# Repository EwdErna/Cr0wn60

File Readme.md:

# Cr0wn60

Cr0wn60 配下の特徴を持つキーボードです。

- TreadStone 配列ベースの左右対称配列
- RP2040 採用の PCB
- Friction O-ring Mount の 3 ピースケース

ファームウェアは以下のリポジトリから取得可能です。  
[Ewderna/qmk_firmware ewderna_22 branch](https://github.com/EwdErna/qmk_firmware/tree/dev/ewderna_22)

## Build Guide

### 同梱物

- PCB
  - デフォルトのファームウェアを書き込み済み
- スイッチプレート
- ケース
  - トップケース
  - ミドルプレート
  - ボトムケース
- O-ring ID185x3.55mm
- Unified Daughter Board S1 / molex Pico EasyMate Cable

> [!Note]  
> ProtoType 版ではスイッチプレート、ケースはデータのみの配布となります。  
> また、O-ring については付属しません。ご自身で購入をお願いします。

### 別途必要なもの

- キースイッチ x60
  - Cherry MX 互換のみ対応
- スタビライザー
  - PCBマウント 2U x3
- LED x15 (Optional)
  - SK6812MINI-E 互換品
- USB Type-C ケーブル
- キーキャップ x60
  - 1U x48
  - 1.25U x5
  - 1.5U x2
  - 1.75U x2
  - 2.25U x3

### 組み立て手順

#### LEDのはんだ付け(Optional)

15個のLEDをはんだ付けします。  

#### スタビライザーの取り付け

PCBにスタビライザーを取り付けます。  
PCB表面にスタビライザーのワイヤー側を示すシルクがあります。  
向きを間違えないよう注意してください。

#### スイッチプレートにキースイッチの取り付け

すべてのキースイッチをスイッチプレートに取り付けます。

#### キースイッチのはんだ付け

プレートごとキースイッチをPCBに取り付け、裏面からはんだ付けします。

#### 動作確認

UDBに付属のケーブルをUDB、PCBそれぞれのハウジングに取り付けます。  
PCとUDBをType-Cケーブルでつなぎ、[Remap](https://remap-keys.app)に接続します。  
CUSTOMIZE YOUR KEYBOARDからCr0wn60を選択したのち、Test Matrixモードを使用し全キーが反応することを確認します。  
オプションのLEDを取り付けている場合もここで確認します。  
> [!TIP]  
> LEDが途中から光らない場合は、光らないLEDかその直前の番号のLEDについてはんだ付けを見直してください。  
> はんだ付けを直しても光らない場合はLEDが壊れている可能性がありますので交換してみてください。

> [!TIP]  
> proto.1、proto.2ではLED番号が逆転しています。LED15が一番最初のLEDで、LED1が一番最後のLEDです。

#### O-ringの取り付け

スイッチプレートとPCBの隙間に、スイッチに引っかかるようにO-ringを取り付けます。  
下側左右の角部分に余裕を持たせるように掛けておくとケースに入れやすくなります。

#### ケースの組み立て

ボトムケース、ミドルプレート、トップケースの順に重ね、ボトムケースの裏側からM3ねじ8本で固定します。  
ミドルプレートの向きに気を付けてください。角の隙間が狭いほうが左側に来るように重ねます。

#### UDBの取り付け

UDBを、付属のねじでボトムケースに固定します。  
付属のケーブルをUDB、PCBのハウジングにそれぞれ取り付けます。向きは特にありません。

#### ケースにPCBの取り付け

PCBをケースに収めます。  
下側左右の角部分に張ったO-ringをトップケースの角に押し付けながら、上側をケース内に押し込みます。  
最後に奥まで押し込んで取付完了です。

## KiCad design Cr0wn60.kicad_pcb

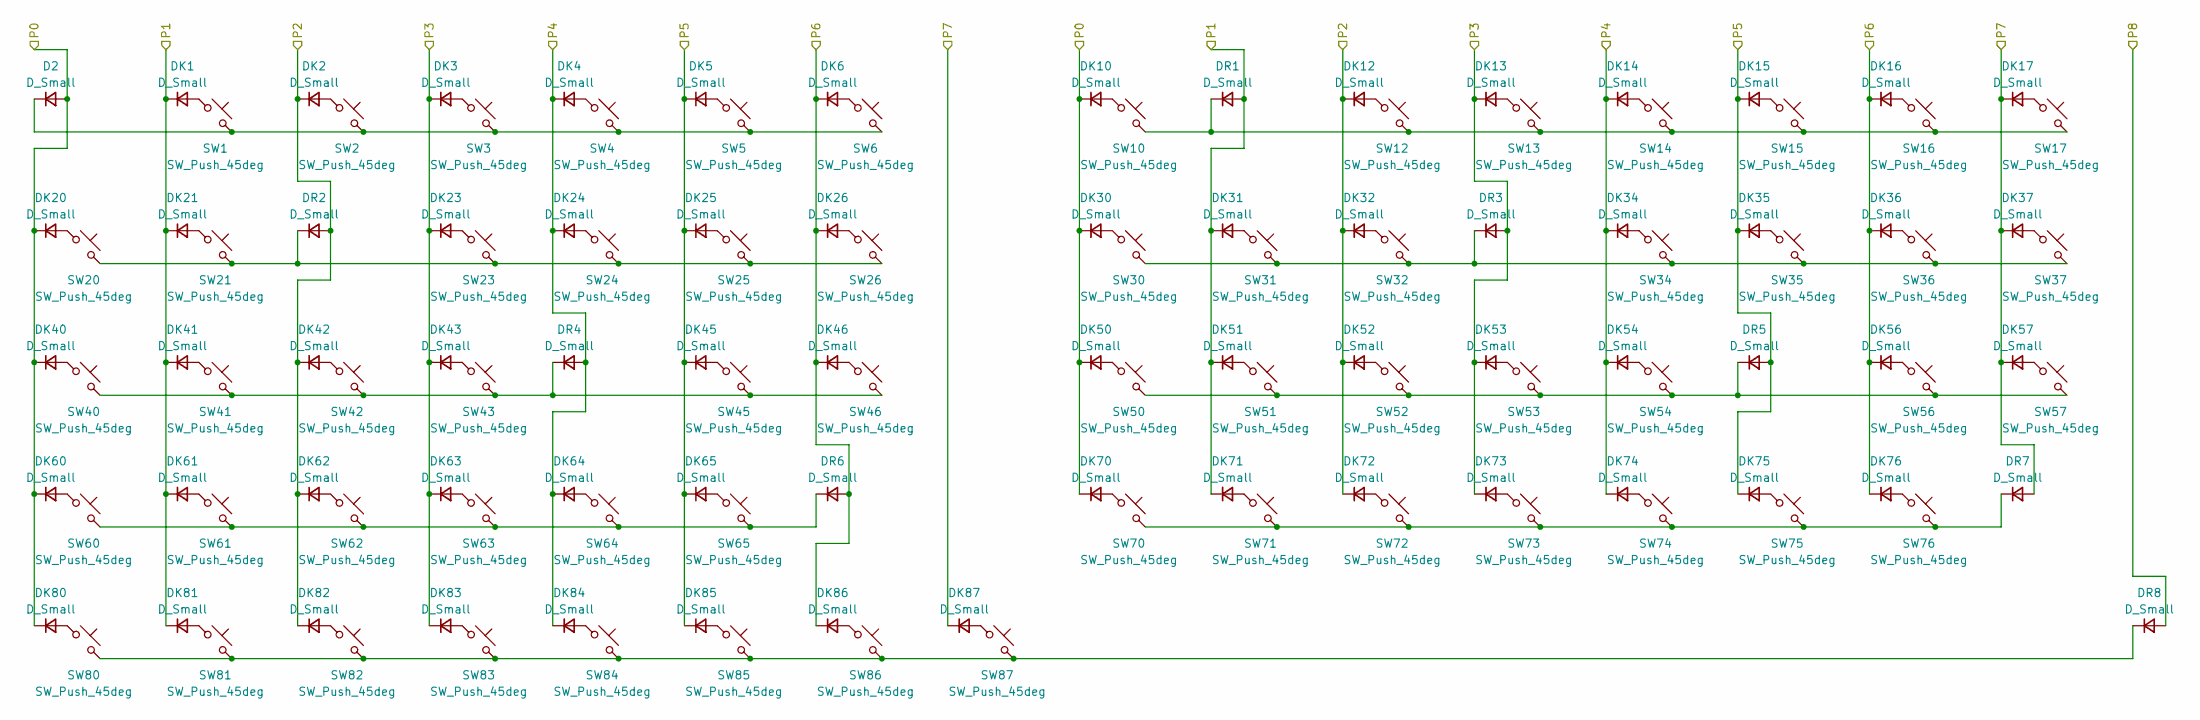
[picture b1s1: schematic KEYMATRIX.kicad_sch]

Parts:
D2: D_Small
DK1, DK2, DK3, DK4, DK5, DK6, DK10, DK12, DK13, DK14, DK15, DK16, DK17, DK20, DK21, DK23, DK24, DK25, DK26, DK30, DK31, DK32, DK34, DK35, DK36, DK37, DK40, DK41, DK42, DK43, DK45, DK46, DK50, DK51, DK52, DK53, DK54, DK56, DK57, DK60, DK61, DK62, DK63, DK64, DK65, DK70, DK71, DK72, DK73, DK74, DK75, DK76, DK80, DK81, DK82, DK83, DK84, DK85, DK86, DK87: D_Small; D_SOD-123
DR1, DR2, DR3, DR4, DR5, DR6, DR7, DR8: D_Small; D_SOD-123
SW1, SW2, SW3, SW4, SW5, SW6, SW10, SW12, SW13, SW14, SW15, SW16, SW17, SW21, SW23, SW24, SW25, SW26, SW30, SW31, SW32, SW34, SW35, SW36, SW41, SW42, SW43, SW45, SW46, SW50, SW51, SW52, SW53, SW54, SW56, SW61, SW62, SW63, SW64, SW65, SW70, SW71, SW72, SW73, SW74, SW75, SW82, SW85: SW_Push_45deg; SW_Cherry_MX1A_1.00u_PCB
SW20, SW37: SW_Push_45deg; SW_Cherry_MX1A_1.50u_PCB
SW40, SW76: SW_Push_45deg; SW_Cherry_MX1A_1.75u_PCB
SW57, SW83, SW84: SW_Push_45deg; SW_Cherry_MX1A_2.25u_PCB
SW60, SW80, SW81, SW86, SW87: SW_Push_45deg; SW_Cherry_MX1A_1.25u_PCB

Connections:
/P0: D2.2 (A), DK10.1 (K), DK20.1 (K), DK30.1 (K), DK40.1 (K), DK50.1 (K), DK60.1 (K), DK70.1 (K), DK80.1 (K); also elsewhere on the board
/P1: DK1.1 (K), DK21.1 (K), DK31.1 (K), DK41.1 (K), DK51.1 (K), DK61.1 (K), DK71.1 (K), DK81.1 (K), DR1.2 (A); also elsewhere on the board
/P2: DK2.1 (K), DK12.1 (K), DK32.1 (K), DK42.1 (K), DK52.1 (K), DK62.1 (K), DK72.1 (K), DK82.1 (K), DR2.2 (A); also elsewhere on the board
/P3: DK3.1 (K), DK13.1 (K), DK23.1 (K), DK43.1 (K), DK53.1 (K), DK63.1 (K), DK73.1 (K), DK83.1 (K), DR3.2 (A); also elsewhere on the board
/P4: DK4.1 (K), DK14.1 (K), DK24.1 (K), DK34.1 (K), DK54.1 (K), DK64.1 (K), DK74.1 (K), DK84.1 (K), DR4.2 (A); also elsewhere on the board
/P5: DK5.1 (K), DK15.1 (K), DK25.1 (K), DK35.1 (K), DK45.1 (K), DK65.1 (K), DK75.1 (K), DK85.1 (K), DR5.2 (A); also elsewhere on the board
/P6: DK6.1 (K), DK16.1 (K), DK26.1 (K), DK36.1 (K), DK46.1 (K), DK56.1 (K), DK76.1 (K), DK86.1 (K), DR6.2 (A); also elsewhere on the board
/P7: DK17.1 (K), DK37.1 (K), DK57.1 (K), DK87.1 (K), DR7.2 (A); also elsewhere on the board
/P8: DR8.2 (A); also elsewhere on the board
unnamed: DK1.2 (A), SW1.1
unnamed: DK2.2 (A), SW2.1
unnamed: DK3.2 (A), SW3.1
unnamed: DK4.2 (A), SW4.1
unnamed: DK5.2 (A), SW5.1
unnamed: DK6.2 (A), SW6.1
unnamed: DK10.2 (A), SW10.1
unnamed: DK12.2 (A), SW12.1
unnamed: DK13.2 (A), SW13.1
unnamed: DK14.2 (A), SW14.1
unnamed: DK15.2 (A), SW15.1
unnamed: DK16.2 (A), SW16.1
unnamed: DK17.2 (A), SW17.1
unnamed: DK20.2 (A), SW20.1
unnamed: DK21.2 (A), SW21.1
unnamed: DK23.2 (A), SW23.1
unnamed: DK24.2 (A), SW24.1
unnamed: DK25.2 (A), SW25.1
unnamed: DK26.2 (A), SW26.1
unnamed: DK30.2 (A), SW30.1
unnamed: DK31.2 (A), SW31.1
unnamed: DK32.2 (A), SW32.1
unnamed: DK34.2 (A), SW34.1
unnamed: DK35.2 (A), SW35.1
unnamed: DK36.2 (A), SW36.1
unnamed: DK37.2 (A), SW37.1
unnamed: DK40.2 (A), SW40.1
unnamed: DK41.2 (A), SW41.1
unnamed: DK42.2 (A), SW42.1
unnamed: DK43.2 (A), SW43.1
unnamed: DK45.2 (A), SW45.1
unnamed: DK46.2 (A), SW46.1
unnamed: DK50.2 (A), SW50.1
unnamed: DK51.2 (A), SW51.1
unnamed: DK52.2 (A), SW52.1
unnamed: DK53.2 (A), SW53.1
unnamed: DK54.2 (A), SW54.1
unnamed: DK56.2 (A), SW56.1
unnamed: DK57.2 (A), SW57.1
unnamed: DK60.2 (A), SW60.1
unnamed: DK61.2 (A), SW61.1
unnamed: DK62.2 (A), SW62.1
unnamed: DK63.2 (A), SW63.1
unnamed: DK64.2 (A), SW64.1
unnamed: DK65.2 (A), SW65.1
unnamed: DK70.2 (A), SW70.1
unnamed: DK71.2 (A), SW71.1
unnamed: DK72.2 (A), SW72.1
unnamed: DK73.2 (A), SW73.1
unnamed: DK74.2 (A), SW74.1
unnamed: DK75.2 (A), SW75.1
unnamed: DK76.2 (A), SW76.1
unnamed: DK80.2 (A), SW80.1
unnamed: DK81.2 (A), SW81.1
unnamed: DK82.2 (A), SW82.1
unnamed: DK83.2 (A), SW83.1
unnamed: DK84.2 (A), SW84.1
unnamed: DK85.2 (A), SW85.1
unnamed: DK86.2 (A), SW86.1
unnamed: DK87.2 (A), SW87.1
unnamed 92: D2.1 (K), SW1.2, SW2.2, SW3.2, SW4.2, SW5.2, SW6.2; also elsewhere on the board
unnamed: DR1.1 (K), SW10.2, SW12.2, SW13.2, SW14.2, SW15.2, SW16.2, SW17.2
unnamed: DR2.1 (K), SW20.2, SW21.2, SW23.2, SW24.2, SW25.2, SW26.2
unnamed: DR3.1 (K), SW30.2, SW31.2, SW32.2, SW34.2, SW35.2, SW36.2, SW37.2
unnamed: DR4.1 (K), SW40.2, SW41.2, SW42.2, SW43.2, SW45.2, SW46.2
unnamed: DR5.1 (K), SW50.2, SW51.2, SW52.2, SW53.2, SW54.2, SW56.2, SW57.2
unnamed: DR6.1 (K), SW60.2, SW61.2, SW62.2, SW63.2, SW64.2, SW65.2
unnamed: DR7.1 (K), SW70.2, SW71.2, SW72.2, SW73.2, SW74.2, SW75.2, SW76.2
unnamed: DR8.1 (K), SW80.2, SW81.2, SW82.2, SW83.2, SW84.2, SW85.2, SW86.2, SW87.2

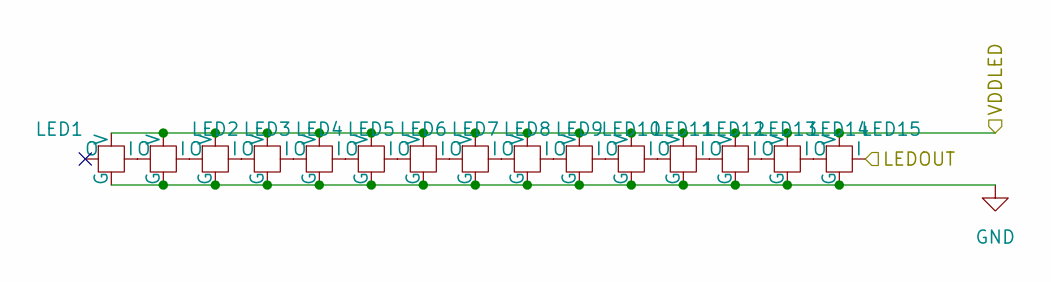
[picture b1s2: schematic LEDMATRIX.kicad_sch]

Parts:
LED1, LED2, LED3, LED4, LED5, LED6, LED7, LED8, LED9, LED10, LED11, LED12, LED13, LED14, LED15: YS-SK6812MINI-E-Small; YS-SK6812MINI-E_rev

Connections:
/LED: LED15.4 (I); also elsewhere on the board
/VDDLED: LED1.1 (V), LED2.1 (V), LED3.1 (V), LED4.1 (V), LED5.1 (V), LED6.1 (V), LED7.1 (V), LED8.1 (V), LED9.1 (V), LED10.1 (V), LED11.1 (V), LED12.1 (V), LED13.1 (V), LED14.1 (V), LED15.1 (V); also elsewhere on the board
GND: LED1.3 (G), LED2.3 (G), LED3.3 (G), LED4.3 (G), LED5.3 (G), LED6.3 (G), LED7.3 (G), LED8.3 (G), LED9.3 (G), LED10.3 (G), LED11.3 (G), LED12.3 (G), LED13.3 (G), LED14.3 (G), LED15.3 (G); also elsewhere on the board
unnamed: LED1.4 (I), LED2.2 (O)
unnamed: LED2.4 (I), LED3.2 (O)
unnamed: LED3.4 (I), LED4.2 (O)
unnamed: LED4.4 (I), LED5.2 (O)
unnamed: LED5.4 (I), LED6.2 (O)
unnamed: LED6.4 (I), LED7.2 (O)
unnamed: LED7.4 (I), LED8.2 (O)
unnamed: LED8.4 (I), LED9.2 (O)
unnamed: LED10.4 (I), LED11.2 (O)
unnamed: LED9.4 (I), LED10.2 (O)
unnamed: LED11.4 (I), LED12.2 (O)
unnamed: LED12.4 (I), LED13.2 (O)
unnamed: LED13.4 (I), LED14.2 (O)
unnamed: LED14.4 (I), LED15.2 (O)

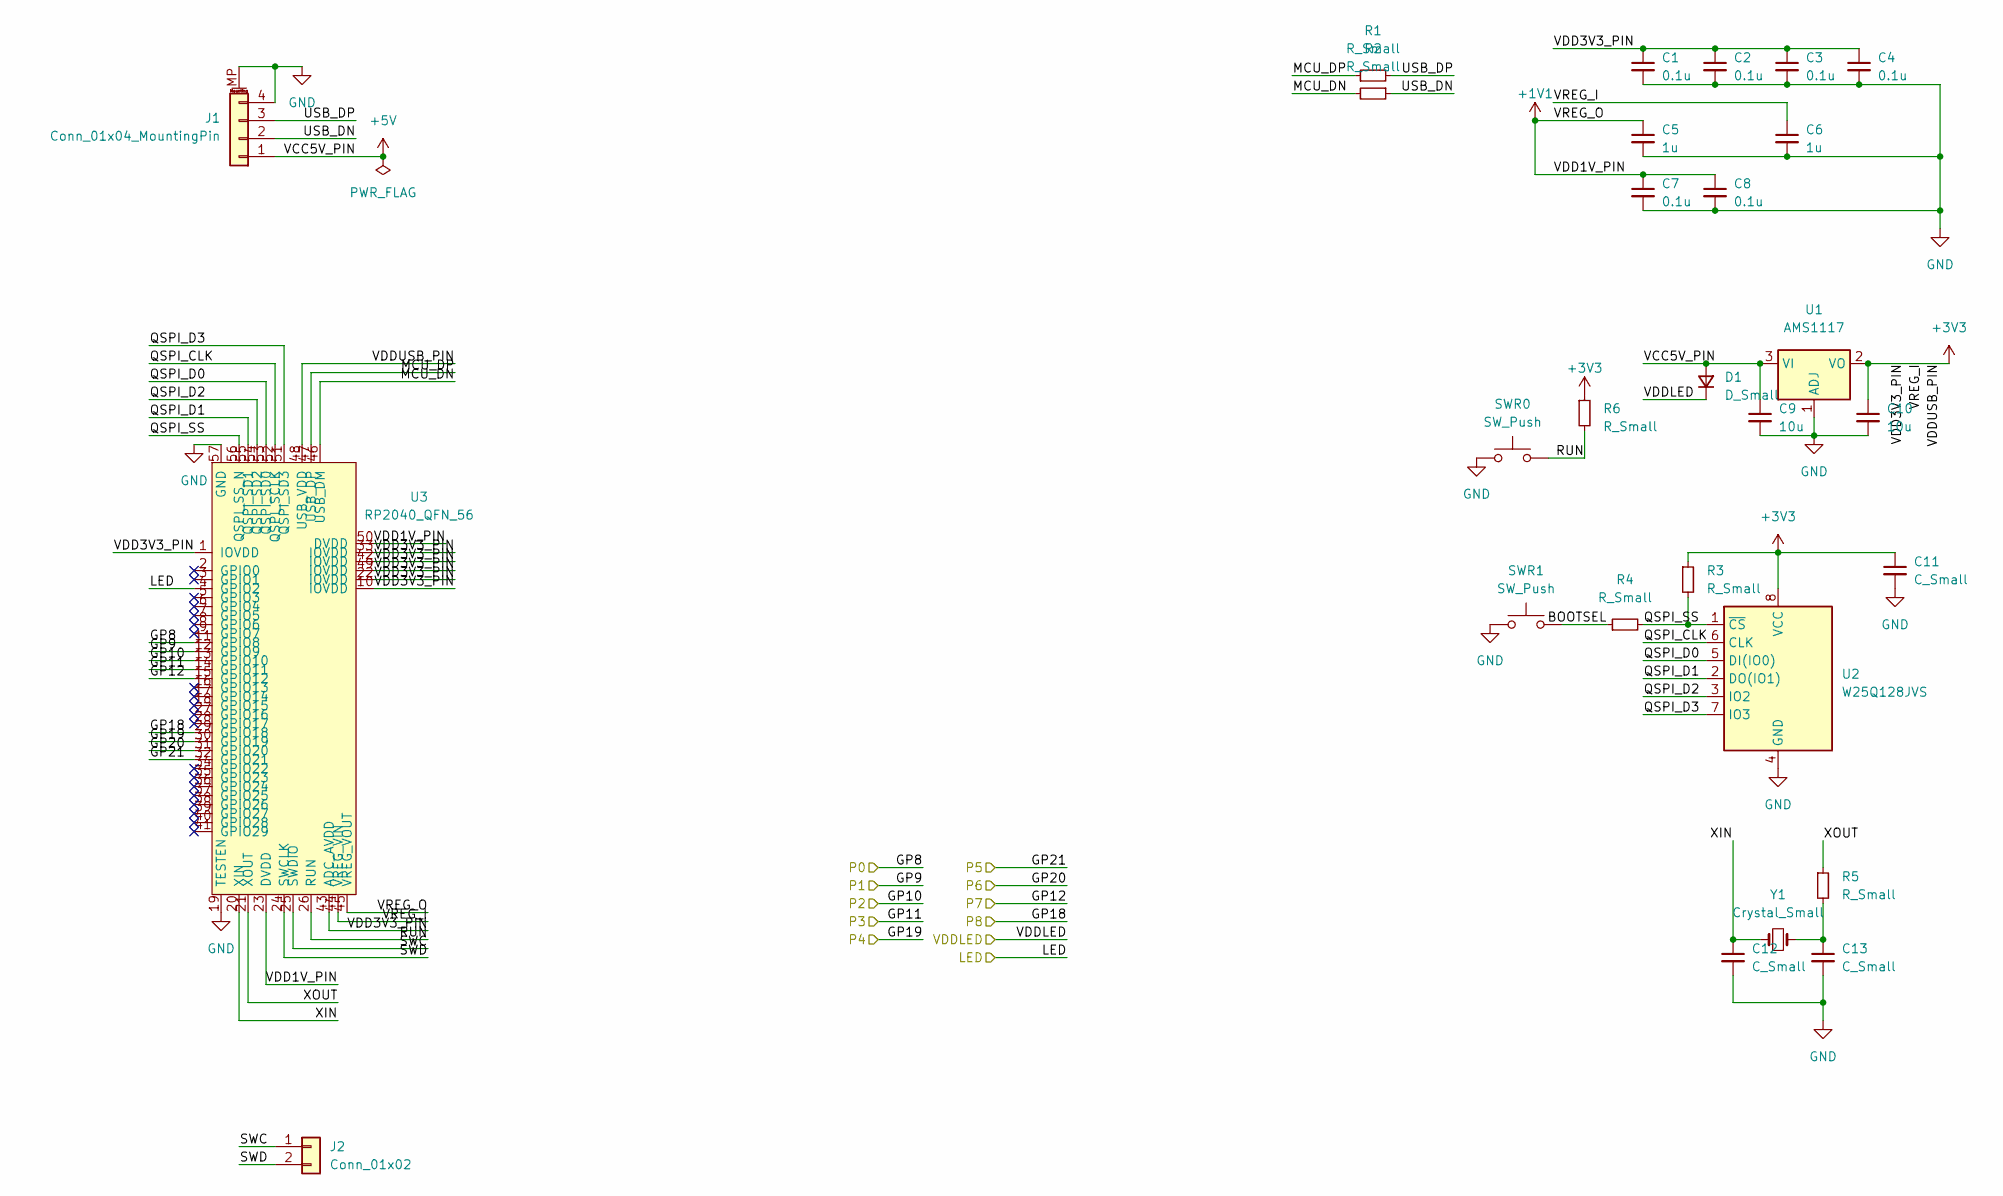
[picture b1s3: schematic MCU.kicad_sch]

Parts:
C1, C2, C3, C4, C7, C8: 0.1u; C_0402_1005Metric
C5, C6: 1u; C_0402_1005Metric
C9, C10: 10u; C_0402_1005Metric
C11, C12, C13: C_Small; C_0402_1005Metric
D1: D_Small; D_SOD-123
J1: Conn_01x04_MountingPin; Pico-EZmate
J2: Conn_01x02; PinSocket_1x02_P1.27mm_Vertical
R1, R2, R3, R4, R5: R_Small; R_0402_1005Metric
R6: R_Small
SWR0, SWR1: SW_Push; TVAF06-A020B-R
U1: AMS1117; SOT-223-3_TabPin2
U2: W25Q128JVS; SOIC-8_5.23x5.23mm_P1.27mm
U3: RP2040_QFN_56; QFN-56-1EP_7x7mm_P0.4mm_EP3.2x3.2mm
Y1: Crystal_Small; Crystal_SMD_3225-4Pin_3.2x2.5mm

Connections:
+1V1: C5.1, C7.1, C8.1, U3.23 (DVDD), U3.45 (VREG_VOUT), U3.50 (DVDD)
+3V3: C1.1, C2.1, C3.1, C4.1, C6.1, C10.1, C11.1, R3.1, R6.1, U1.2 (VO), U2.8 (VCC), U3.1 (IOVDD), U3.10 (IOVDD), U3.22 (IOVDD), U3.33 (IOVDD), U3.42 (IOVDD), U3.43 (ADC_AVDD), U3.44 (VREG_VIN), U3.48 (USB_VDD), U3.49 (IOVDD)
+5V: C9.1, D1.2 (A), J1.1, U1.3 (VI)
/LED: U3.4 (GPIO2); also elsewhere on the board
/MCU/BOOTSEL: R4.1, SWR1.2
/MCU/MCU_DN: R2.2, U3.46 (USB_DM)
/MCU/MCU_DP: R1.1, U3.47 (USB_DP)
/MCU/QSPI_CLK: U2.6 (CLK), U3.52 (QSPI_SCLK)
/MCU/QSPI_D0: U2.5 (DI(IO0)), U3.53 (QSPI_SD0)
/MCU/QSPI_D1: U2.2 (DO(IO1)), U3.55 (QSPI_SD1)
/MCU/QSPI_D2: U2.3 (IO2), U3.54 (QSPI_SD2)
/MCU/QSPI_D3: U2.7 (IO3), U3.51 (QSPI_SD3)
/MCU/QSPI_SS: R3.2, R4.2, U2.1 (~CS), U3.56 (QSPI_SS_N)
/MCU/RUN: R6.2, SWR0.2, U3.26 (RUN)
/MCU/SWC: J2.1, U3.25 (SWDIO)
/MCU/SWD: J2.2, U3.24 (SWCLK)
/MCU/USB_DN: J1.2, R2.1
/MCU/USB_DP: J1.3, R1.2
/MCU/XIN: C12.1, U3.20 (XIN), Y1.1
/MCU/XOUT: R5.1, U3.21 (XOUT)
/P0: U3.11 (GPIO8); also elsewhere on the board
/P1: U3.12 (GPIO9); also elsewhere on the board
/P2: U3.13 (GPIO10); also elsewhere on the board
/P3: U3.14 (GPIO11); also elsewhere on the board
/P4: U3.30 (GPIO19); also elsewhere on the board
/P5: U3.32 (GPIO21); also elsewhere on the board
/P6: U3.31 (GPIO20); also elsewhere on the board
/P7: U3.15 (GPIO12); also elsewhere on the board
/P8: U3.29 (GPIO18); also elsewhere on the board
/VDDLED: D1.1 (K); also elsewhere on the board
GND: C1.2, C2.2, C3.2, C4.2, C5.2, C6.2, C7.2, C8.2, C9.2, C10.2, C11.2, C12.2, C13.2, J1.4, J1.MP (MountPin), SWR0.1, SWR1.1, U1.1 (ADJ), U2.4 (GND), U3.19 (TESTEN), U3.57 (GND); also elsewhere on the board
unnamed: C13.1, R5.2, Y1.2

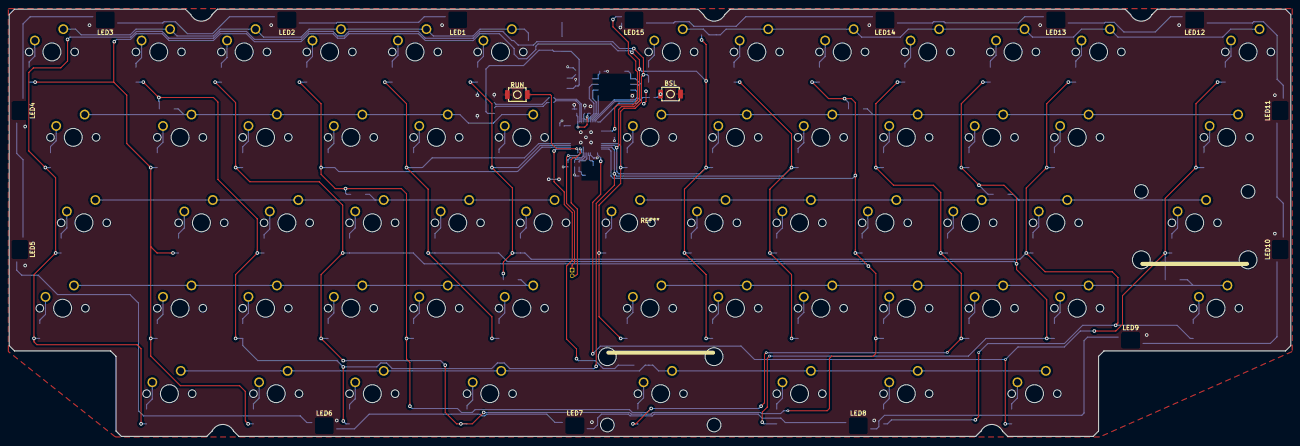
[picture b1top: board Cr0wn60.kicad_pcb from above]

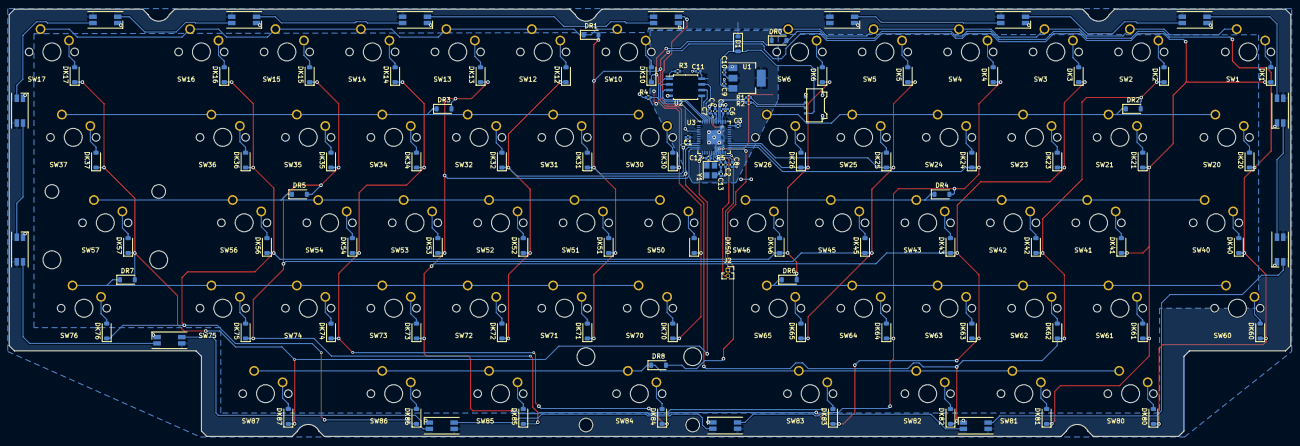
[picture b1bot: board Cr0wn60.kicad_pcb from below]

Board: 2 copper layers, 285.8 x 95.2 mm, 171 parts (109 on the bottom side), 115 nets.

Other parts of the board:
DR0: D_Small; D_SOD-123

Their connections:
/P0: DR0.2 (A); also elsewhere on the board
unnamed 92: DR0.1 (K); also elsewhere on the board

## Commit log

2023-06-17 add production files
2023-07-02 add Case data
2023-07-09 wip: UDB-S1
2023-07-15 redesign
2023-07-15 redesign (今度こそ)
2023-12-02 finished redesign
2023-12-02 corrected gitignore
2024-04-03 add Readme.md
2024-04-03 fix br
2024-04-04 ファイルを整理
2024-04-06 Add size info and proto notation about o-ring
2024-10-06 some tweak
2024-12-05 update KiCAD 7->8
2025-06-18 fix: git ignore for large files
2025-06-18 wip: 20250618
